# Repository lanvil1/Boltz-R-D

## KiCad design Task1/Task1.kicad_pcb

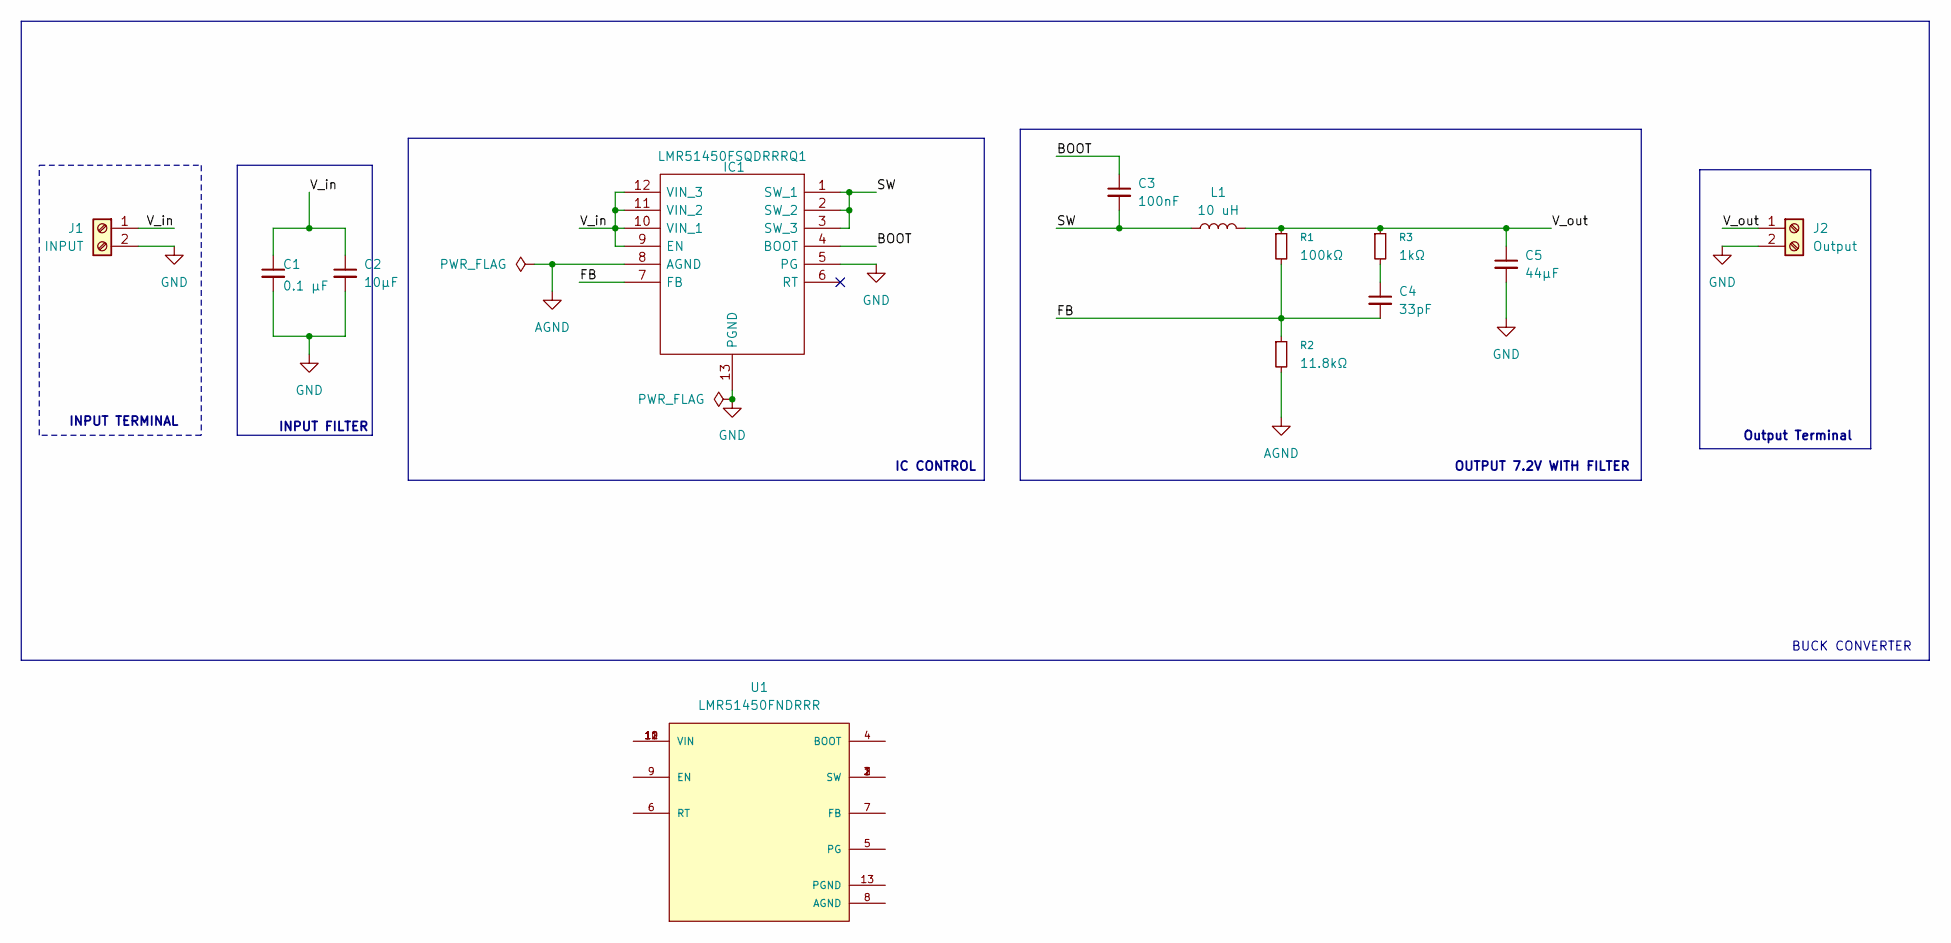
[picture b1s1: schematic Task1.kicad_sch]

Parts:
C1: 0.1 µF; C_0805_2012Metric
C2: 10µF; C_0805_2012Metric
C3: 100nF; C_0603_1608Metric
C4: 33pF; C_0603_1608Metric
C5: 44µF; C_0805_2012Metric
IC1: LMR51450FSQDRRRQ1; SON50P300X300X80-13N-D; Mouser Part Number 595-LMR51450FSQDRRQ1
J1: INPUT; TerminalBlock_Altech_AK300-2_P5.00mm
J2: Output; TerminalBlock_Altech_AK300-2_P5.00mm
L1: 10 uH; L_1210_3225Metric
R1: 100kΩ; R_0603_1608Metric
R2: 11.8kΩ; R_0603_1608Metric
R3: 1kΩ; R_0603_1608Metric
U1: LMR51450FNDRRR; CONV_LMR51450FNDRRR; PARTREV December 2022

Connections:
/BOOT: C3.1, IC1.4 (BOOT)
/FB: C4.2, IC1.7 (FB), R1.2, R2.1
/SW: C3.2, IC1.1 (SW_1), IC1.2 (SW_2), IC1.3 (SW_3), L1.1
/V_in: C1.1, C2.1, IC1.9 (EN), IC1.10 (VIN_1), IC1.11 (VIN_2), IC1.12 (VIN_3), J1.1
/V_out: C5.1, J2.1, L1.2, R1.1, R3.1
AGND: IC1.8 (AGND), R2.2
GND: C1.2, C2.2, C5.2, IC1.5 (PG), IC1.13 (PGND), J1.2, J2.2
unnamed: C4.1, R3.2
unnamed: U1.1 (SW), U1.2 (SW), U1.3 (SW)
unnamed: U1.10 (VIN), U1.11 (VIN), U1.12 (VIN)

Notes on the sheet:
BUCK CONVERTER
INPUT FILTER
Output Terminal
INPUT TERMINAL
OUTPUT 7.2V WITH FILTER
IC CONTROL

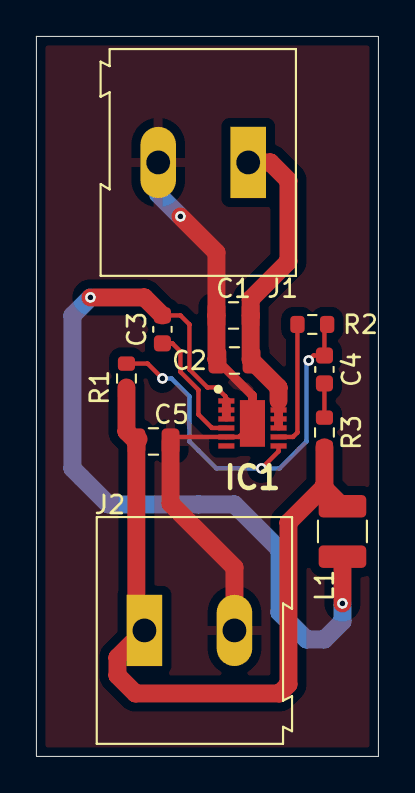
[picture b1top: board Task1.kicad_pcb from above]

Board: 2 copper layers, 19.0 x 40.0 mm, 12 parts (0 on the bottom side), 8 nets.
